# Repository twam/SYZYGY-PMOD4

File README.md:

SYZYGY-PMOD4
===

Board for adapting a [SYZYGY](https://syzygyfpga.io) Standard compatible port to four [Pmod™](https://digilent.com/reference/pmod/) compatible ports.
It is based on [SZG-PMOD4](https://opalkelly.com/products/szg-pmod4/) by [Opal Kelly](https://opalkelly.com).

### Images

### Firmware

The board is compatible with the [avr-dna-fw](https://github.com/SYZYGYfpga/avr-dna-fw) reference firmware.

### JLCPCB

PCBs can be ordered fully-assembled (besides the High-Speed connector on the bottom side and the pin headers) from [JLCPCB](https://jlcpcb.com/DDE). Required files are
[SYZYGY-PMOD4_bom_jlc.csv](Gerber/SYZYGY-PMOD4_bom_jlc.csv), [SYZYGY-PMOD4_cpl_jlc.csv](Gerber/SYZYGY-PMOD4_cpl_jlc.csv) and
[SYZYGY-PMOD4.zip](SYZYGY-PMOD4.zip).

## License

[![CC BY-SA 4.0][cc-by-sa-shield]][cc-by-sa]

This work is licensed under a [Creative Commons Attribution-NonCommercial-ShareAlike 4.0 International License][cc-by-sa].

[![CC BY-SA 4.0][cc-by-sa-image]][cc-by-sa]

[cc-by-sa]: http://creativecommons.org/licenses/by-nc-sa/4.0/
[cc-by-sa-image]: https://licensebuttons.net/l/by-nc-sa/4.0/88x31.png
[cc-by-sa-shield]: https://img.shields.io/badge/License-CC%20BY--NC--SA%204.0-lightgrey.svg

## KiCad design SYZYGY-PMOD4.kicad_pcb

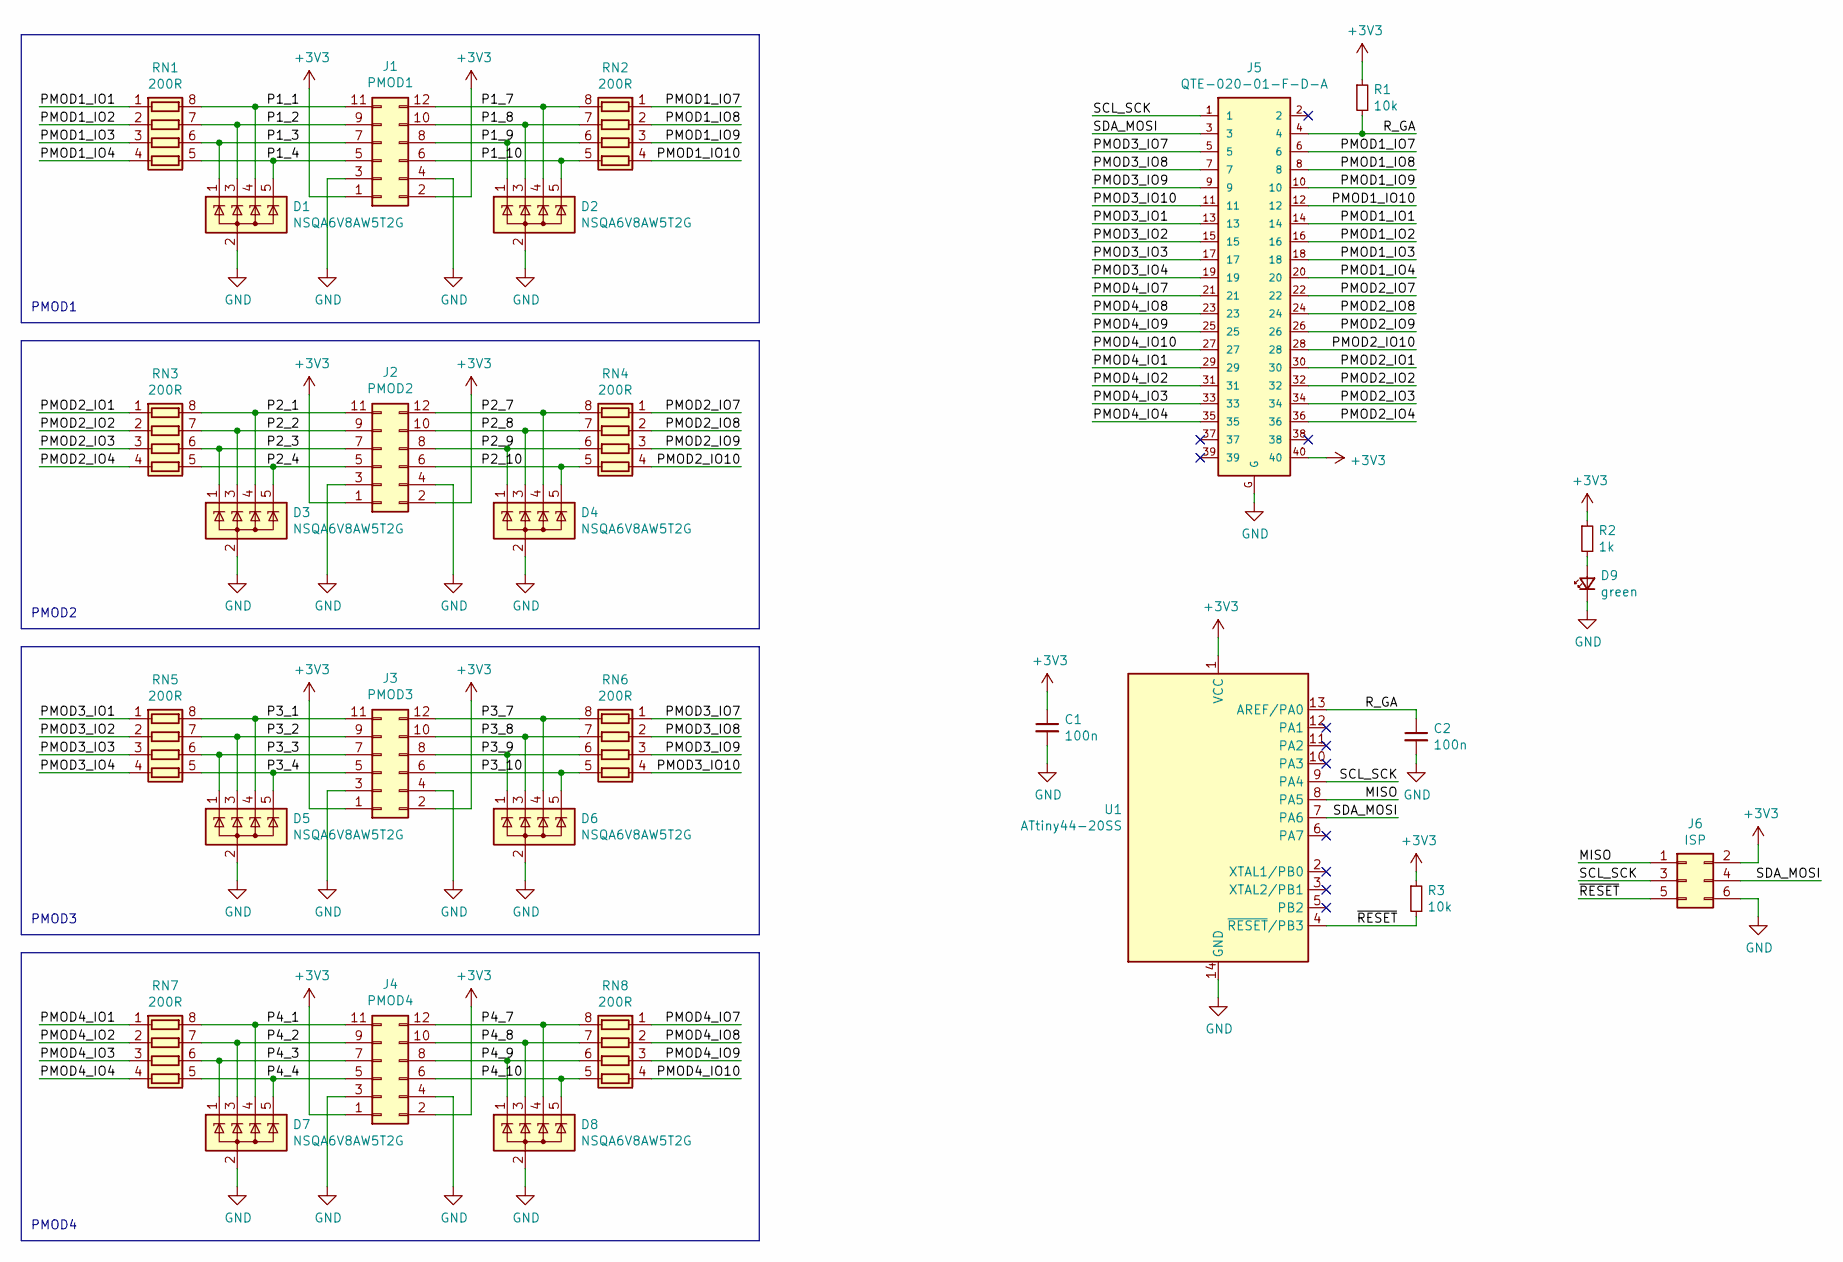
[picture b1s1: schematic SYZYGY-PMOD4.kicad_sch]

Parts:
C1, C2: 100n; C_0603_1608Metric; LCSC C14663
D1, D2, D3, D4, D5, D6, D7, D8: NSQA6V8AW5T2G; SOT-353_SC-70-5; LCSC C233419
D9: green; LED_0603_1608Metric; LCSC C72043
J1: PMOD1; PinSocket_2x06_P2.54mm_Horizontal
J2: PMOD2; PinSocket_2x06_P2.54mm_Horizontal
J3: PMOD3; PinSocket_2x06_P2.54mm_Horizontal
J4: PMOD4; PinSocket_2x06_P2.54mm_Horizontal
J5: QTE-020-01-F-D-A
J6: ISP; Tag-Connect_TC2030-IDC-NL_2x03_P1.27mm_Vertical
R1, R3: 10k; R_0603_1608Metric; LCSC C25804
R2: 1k; R_0603_1608Metric; LCSC C21190
RN1, RN2, RN3, RN4, RN5, RN6, RN7, RN8: 200R; R_Array_Convex_4x0603; LCSC C29486
U1: ATtiny44-20SS; SOIC-14_3.9x8.7mm_P1.27mm; LCSC C23640

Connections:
+3V3: C1.1, J1.1, J1.2, J2.1, J2.2, J3.1, J3.2, J4.1, J4.2, J5.40, J6.2, R1.1, R2.1, R3.1, U1.1 (VCC)
/MISO: J6.1, U1.8 (PA5)
/P1_1: D1.4 (K), J1.11, RN1.8 (R1.2)
/P1_2: D1.3 (K), J1.9, RN1.7 (R2.2)
/P1_3: D1.1 (K), J1.7, RN1.6 (R3.2)
/P1_4: D1.5 (K), J1.5, RN1.5 (R4.2)
/P1_7: D2.4 (K), J1.12, RN2.8 (R1.2)
/P1_8: D2.3 (K), J1.10, RN2.7 (R2.2)
/P1_9: D2.1 (K), J1.8, RN2.6 (R3.2)
/P1_10: D2.5 (K), J1.6, RN2.5 (R4.2)
/P2_1: D3.4 (K), J2.11, RN3.8 (R1.2)
/P2_2: D3.3 (K), J2.9, RN3.7 (R2.2)
/P2_3: D3.1 (K), J2.7, RN3.6 (R3.2)
/P2_4: D3.5 (K), J2.5, RN3.5 (R4.2)
/P2_7: D4.4 (K), J2.12, RN4.8 (R1.2)
/P2_8: D4.3 (K), J2.10, RN4.7 (R2.2)
/P2_9: D4.1 (K), J2.8, RN4.6 (R3.2)
/P2_10: D4.5 (K), J2.6, RN4.5 (R4.2)
/P3_1: D5.4 (K), J3.11, RN5.8 (R1.2)
/P3_2: D5.3 (K), J3.9, RN5.7 (R2.2)
/P3_3: D5.1 (K), J3.7, RN5.6 (R3.2)
/P3_4: D5.5 (K), J3.5, RN5.5 (R4.2)
/P3_7: D6.4 (K), J3.12, RN6.8 (R1.2)
/P3_8: D6.3 (K), J3.10, RN6.7 (R2.2)
/P3_9: D6.1 (K), J3.8, RN6.6 (R3.2)
/P3_10: D6.5 (K), J3.6, RN6.5 (R4.2)
/P4_1: D7.4 (K), J4.11, RN7.8 (R1.2)
/P4_2: D7.3 (K), J4.9, RN7.7 (R2.2)
/P4_3: D7.1 (K), J4.7, RN7.6 (R3.2)
/P4_4: D7.5 (K), J4.5, RN7.5 (R4.2)
/P4_7: D8.4 (K), J4.12, RN8.8 (R1.2)
/P4_8: D8.3 (K), J4.10, RN8.7 (R2.2)
/P4_9: D8.1 (K), J4.8, RN8.6 (R3.2)
/P4_10: D8.5 (K), J4.6, RN8.5 (R4.2)
/PMOD1_IO1: J5.14, RN1.1 (R1.1)
/PMOD1_IO2: J5.16, RN1.2 (R2.1)
/PMOD1_IO3: J5.18, RN1.3 (R3.1)
/PMOD1_IO4: J5.20, RN1.4 (R4.1)
/PMOD1_IO7: J5.6, RN2.1 (R1.1)
/PMOD1_IO8: J5.8, RN2.2 (R2.1)
/PMOD1_IO9: J5.10, RN2.3 (R3.1)
/PMOD1_IO10: J5.12, RN2.4 (R4.1)
/PMOD2_IO1: J5.30, RN3.1 (R1.1)
/PMOD2_IO2: J5.32, RN3.2 (R2.1)
/PMOD2_IO3: J5.34, RN3.3 (R3.1)
/PMOD2_IO4: J5.36, RN3.4 (R4.1)
/PMOD2_IO7: J5.22, RN4.1 (R1.1)
/PMOD2_IO8: J5.24, RN4.2 (R2.1)
/PMOD2_IO9: J5.26, RN4.3 (R3.1)
/PMOD2_IO10: J5.28, RN4.4 (R4.1)
/PMOD3_IO1: J5.13, RN5.1 (R1.1)
/PMOD3_IO2: J5.15, RN5.2 (R2.1)
/PMOD3_IO3: J5.17, RN5.3 (R3.1)
/PMOD3_IO4: J5.19, RN5.4 (R4.1)
/PMOD3_IO7: J5.5, RN6.1 (R1.1)
/PMOD3_IO8: J5.7, RN6.2 (R2.1)
/PMOD3_IO9: J5.9, RN6.3 (R3.1)
/PMOD3_IO10: J5.11, RN6.4 (R4.1)
/PMOD4_IO1: J5.29, RN7.1 (R1.1)
/PMOD4_IO2: J5.31, RN7.2 (R2.1)
/PMOD4_IO3: J5.33, RN7.3 (R3.1)
/PMOD4_IO4: J5.35, RN7.4 (R4.1)
/PMOD4_IO7: J5.21, RN8.1 (R1.1)
/PMOD4_IO8: J5.23, RN8.2 (R2.1)
/PMOD4_IO9: J5.25, RN8.3 (R3.1)
/PMOD4_IO10: J5.27, RN8.4 (R4.1)
/R_GA: C2.1, J5.4, R1.2, U1.13 (AREF/PA0)
/SCL_SCK: J5.1, J6.3, U1.9 (PA4)
/SDA_MOSI: J5.3, J6.4, U1.7 (PA6)
/~RESET: J6.5, R3.2, U1.4 (~RESET/PB3)
GND: C1.2, C2.2, D1.2 (A), D2.2 (A), D3.2 (A), D4.2 (A), D5.2 (A), D6.2 (A), D7.2 (A), D8.2 (A), D9.1 (K), J1.3, J1.4, J2.3, J2.4, J3.3, J3.4, J4.3, J4.4, J5.G, J6.6, U1.14 (GND)
unnamed: D9.2 (A), R2.2

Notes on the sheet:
PMOD3
PMOD1
PMOD4
PMOD2

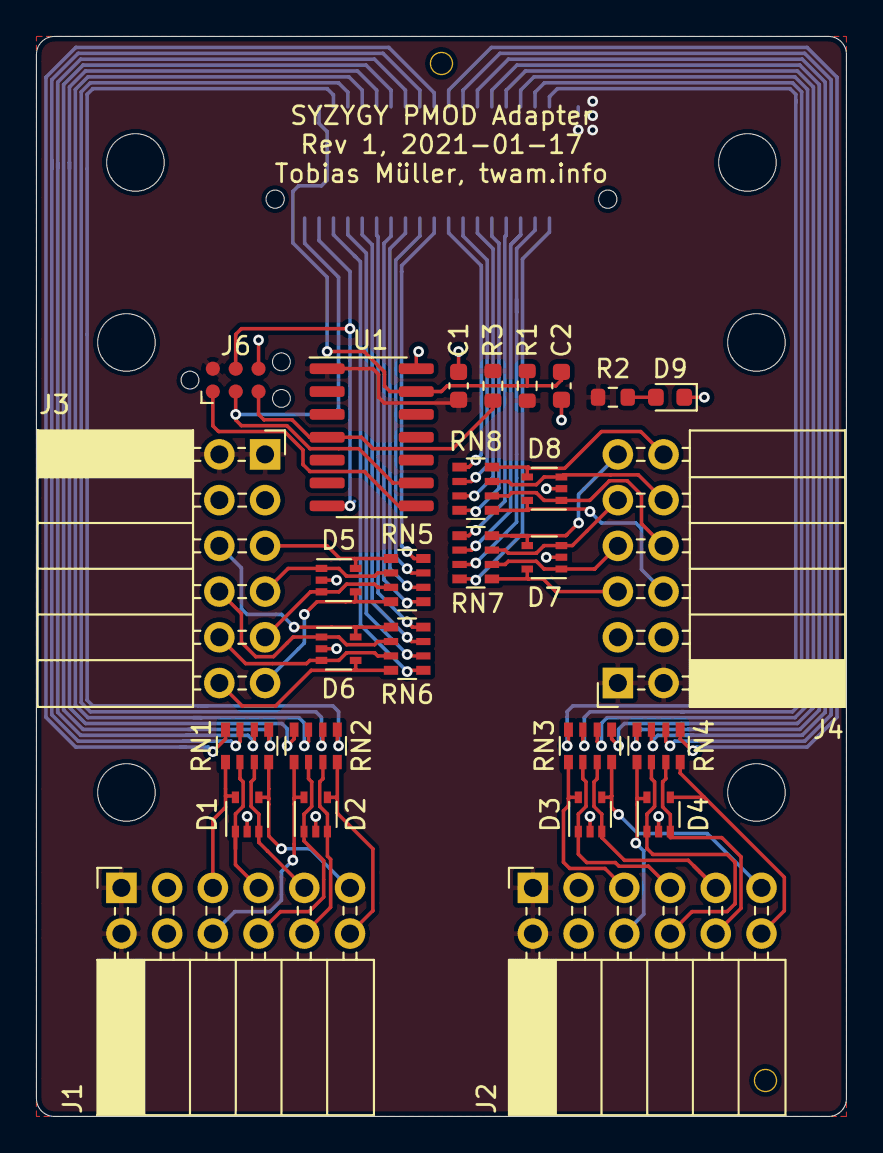
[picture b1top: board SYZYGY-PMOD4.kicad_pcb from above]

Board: 2 copper layers, 45.0 x 60.0 mm, 29 parts (1 on the bottom side), 72 nets.

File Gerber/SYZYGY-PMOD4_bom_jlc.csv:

"Comment","Designator","Footprint","LCSC Part #"
"100n","C2,C1","C_0603_1608Metric","C14663"
"NSQA6V8AW5T2G","D2,D3,D4,D5,D6,D7,D8,D1","SOT-353_SC-70-5","C233419"
"green","D9","LED_0603_1608Metric","C72043"
"10k","R1,R3","R_0603_1608Metric","C25804"
"1k","R2","R_0603_1608Metric","C21190"
"200R","RN1,RN2,RN3,RN4,RN5,RN6,RN7,RN8","R_Array_Convex_4x0603","C29486"
"ATtiny44-20SS","U1","SOIC-14_3.9x8.7mm_P1.27mm","C23640"

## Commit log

2022-01-07 Initial commit. Rev1.
2022-01-07 Add schematic Rev1
2022-01-07 Update to KiCad 6
2022-01-07 Add README
2022-01-08 Add link to reference firmware
2022-01-16 Remove note that design is untested.
2022-01-17 Add images
